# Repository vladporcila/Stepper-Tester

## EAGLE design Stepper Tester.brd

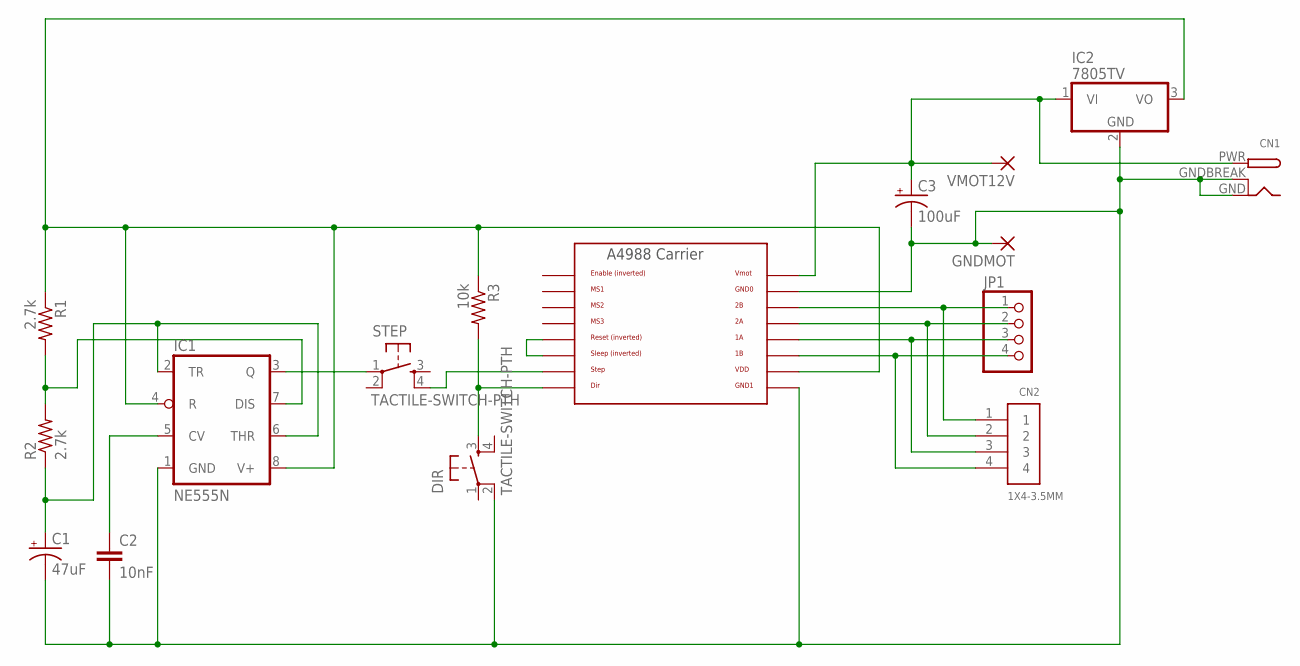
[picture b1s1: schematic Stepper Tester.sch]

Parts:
C1: 47uF; B45181B
C2: 10nF; C050-024X044
C3: 100uF; E3,5-10
CN1: DCBARRELPTH; DCJACK_2MM_PTH
CN2: 1X4-3.5MM; 1X04-3.5MM
DIR: TACTILE-SWITCH-PTH; TAC-SWITCH-PTH
GNDMOT: 3,81/1,4
IC1: NE555N; DIL08-ROUND
IC2: 7805TV; TO220V
JP1: PINHD-1X4; 1X04
R1, R2: 2.7k; 0414/15
R3: 10k; 0414/15
STEP: TACTILE-SWITCH-PTH; TAC-SWITCH-PTH
U$1: A4983CARRIER; A4988BREAKOUT
VMOT12V: 3,81/1,4

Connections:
unnamed: C2.1, IC1.5 (CV)
unnamed: C1.+, IC1.2 (TR), IC1.6 (THR), R2.1
unnamed: IC1.7 (DIS), R1.2, R2.2
unnamed: IC1.4 (R), IC1.8 (V+), IC2.3 (VO), R1.1, R3.1, U$1.VDD
unnamed: IC1.3 (Q), STEP.1
unnamed: STEP.4, U$1.STEP
unnamed: CN2.2, JP1.2, U$1.2A
unnamed: CN2.3, JP1.3, U$1.1A
unnamed: U$1.RST, U$1.SLP (SLEEP)
unnamed: DIR.3, R3.2, U$1.DIR
unnamed: CN2.1, JP1.1, U$1.2B
unnamed: CN2.4, JP1.4, U$1.1B
unnamed: C3.+, CN1.PWR, IC2.1 (VI), U$1.VMOT, VMOT12V.1
unnamed: C1.-, C2.2, C3.-, CN1.GND, CN1.GNDBREAK, DIR.2, GNDMOT.1, IC1.1 (GND), IC2.2 (GND), U$1.GND0, U$1.GND1

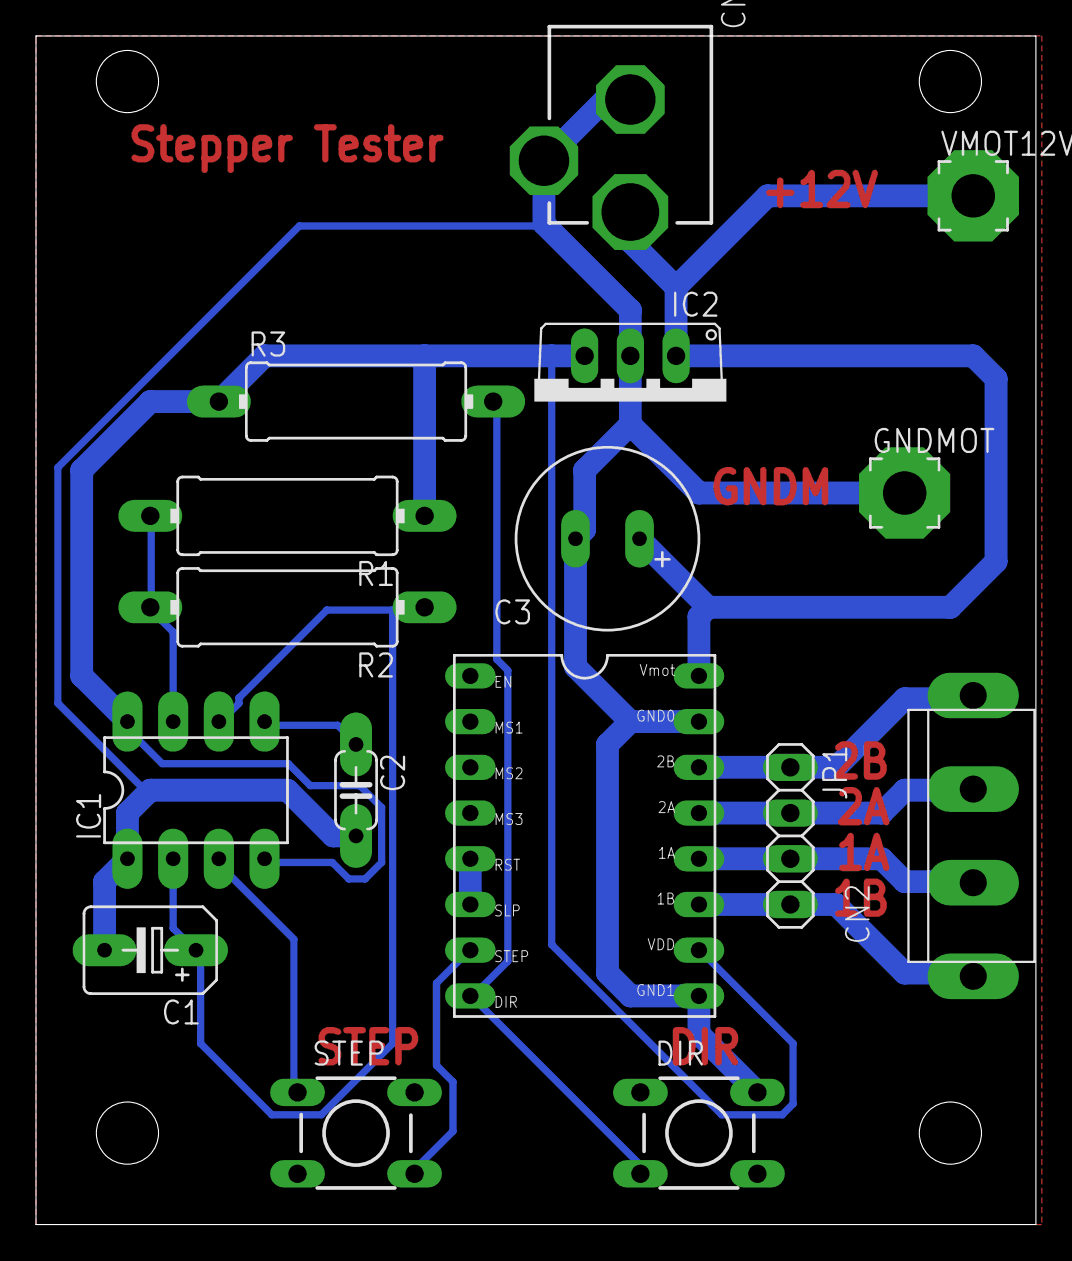
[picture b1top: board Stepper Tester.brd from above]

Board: 2 copper layers, 55.5 x 66.0 mm, 16 parts (0 on the bottom side), 14 nets.

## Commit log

2016-09-29 :lollipop: Added .gitattributes & .gitignore files
2016-09-29 Stepper tester
    Stepper tester

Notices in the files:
parts and their libraries:
GeekAmmo: Licensing:Creative Commons ShareAlike 4.0 International - https://creativecommons.org/licenses/by-sa/4.0
